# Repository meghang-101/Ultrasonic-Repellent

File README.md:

# Ultrasonic-Repellent
Eagle Cad Design with Gerber Files

The [Schematic](https://github.com/meghang-101/Ultrasonic-Repellent/blob/main/20-12-2020-10pm.pdf) has the Schematic Representation of the Circuit connections including the Ultrasonic Repellent and the Battery Indicator

The [Eagle Schematic](https://github.com/meghang-101/Ultrasonic-Repellent/blob/main/20-12-2020-10pm.sch) and the [Eagle Board](https://github.com/meghang-101/Ultrasonic-Repellent/blob/main/20-12-2020-10pm.brd) has the Eagle files for the Schematic and Board respectively.

The [Gerber Files](https://github.com/meghang-101/Ultrasonic-Repellent/blob/main/NewGerberFiles.zip) has the Gerber Files of the PCB which are necessary for manufacturing and fabrication.

# Components
1) 555 IC

2) Capacitors: 10nF(Ceramic), 10uF(Polarized)

3) Resistors: 47k, 1.2k, 10k, 47k, 330R

4) Zener Diode: 6.2V

5) LEDs: Red, Green

6) Transistors: C945 (x2)

7) 9V Battery

8) SPST Switch

9) Speaker/ Buzzer

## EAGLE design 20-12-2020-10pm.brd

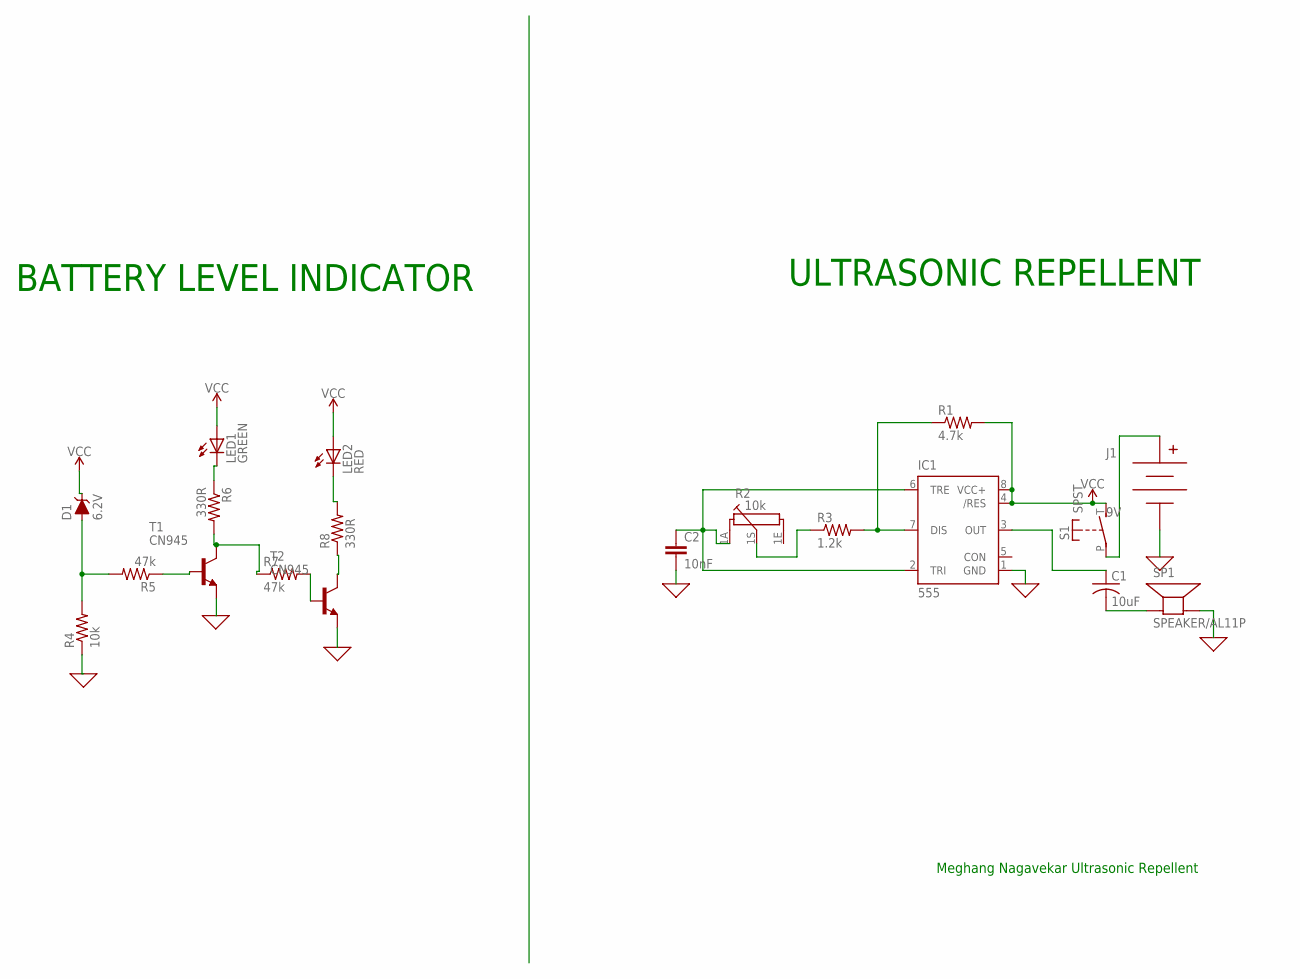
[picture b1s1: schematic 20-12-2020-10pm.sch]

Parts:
C1: 10uF; C0805
C2: 10nF; 0603
D1: 6.2V; SOD-323
IC1: 555; SO08
J1: 9V; BC9VPC
LED1: GREEN; LED5MM
LED2: RED; LED5MM
R1: 4.7k; R0805
R2: 10k; PC16S
R3: 1.2k; R0805
R4: 10k; R0805
R5, R7: 47k; R0805
R6, R8: 330R; R0805
S1: SPST; JUDCOSPST
SP1: SPEAKER/AL11P; AL11P
T1, T2: CN945; TO92-EBC-OVAL

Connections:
0: C2.2, IC1.1 (GND), J1.V-, R4.1, SP1.-, T1.E, T2.E
unnamed: J1.V+, S1.P
unnamed: IC1.7 (DIS), R1.1, R3.2
unnamed: C1.1, IC1.3 (OUT)
unnamed: C1.2, SP1.+
unnamed: R2.1S, R3.1
unnamed: C2.1, IC1.2 (TRI), IC1.6 (TRE), R2.1A
unnamed: D1.A, R4.2, R5.2
unnamed: R5.1, T1.B
unnamed: R6.2, R7.1, T1.C
unnamed: R7.2, T2.B
unnamed: R8.1, T2.C
unnamed: LED1.K (C), R6.1
unnamed: LED2.K (C), R8.2
VCC: D1.C, IC1.4 (/RES), IC1.8 (VCC+), LED1.A, LED2.A, R1.2, S1.T (S)

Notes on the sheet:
BATTERY LEVEL INDICATOR
ULTRASONIC REPELLENT
Meghang Nagavekar Ultrasonic Repellent

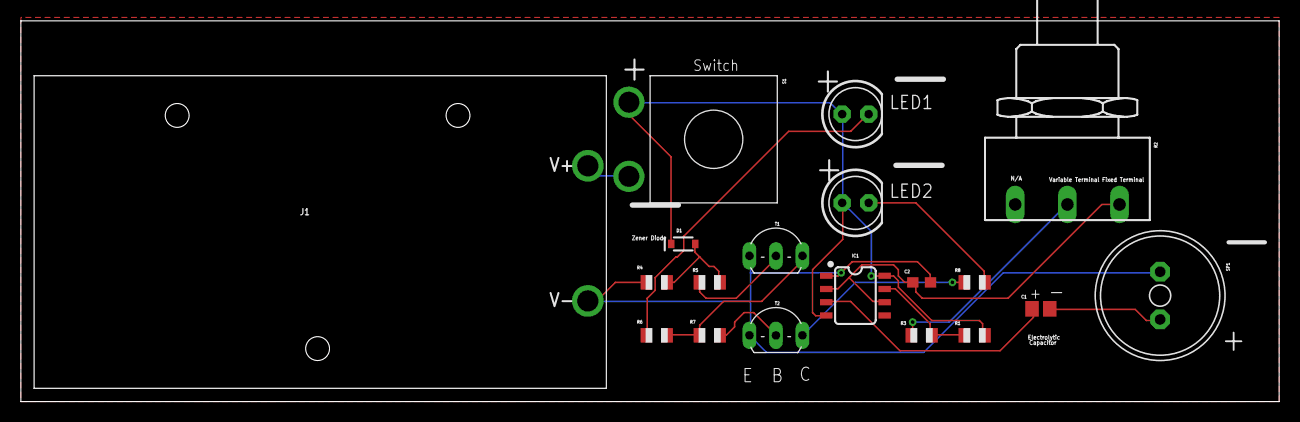
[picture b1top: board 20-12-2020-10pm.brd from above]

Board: 2 copper layers, 120.6 x 36.5 mm, 19 parts (0 on the bottom side), 15 nets.

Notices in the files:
parts and their libraries:
SparkFun-Capacitors: Licensing: Creative Commons ShareAlike 4.0 International - https://creativecommons.org/licenses/by-sa/4.0
